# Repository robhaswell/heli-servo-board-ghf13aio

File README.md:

# Helicopter servo bus board
This project is a PCB designed to facilitate wiring a helicopter servo bus to a drone flight controller.

Mounting pattern: 16x16mm

The flight controller in mind when designing this PCB was a [GHF13AIO](https://www.aliexpress.com/af/ghf13aio.html).
This bus supports 3 servo outputs and so must be used for helicopters with a motor-driven tail connected to an ESC.

The connector footprints are for 1.25mm pitch connectors, such as Molex PicoBlade or JST 1.25.

**Please read the [assembly instructions](#assembly-instructions) before ordering or use**

## Instructions for ordering

First: Read the [assembly instructions](#assembly-instructions) and determine that this board is suitable for your setup.

You can order this PCB with a prototyping service.
Below are instructions for using [JLCPCB](https://jlcpcb.com):

1. Visit https://jlcpcb.com/.
2. Click "Order now' from the menu - do not use the quoting box.
3. Upload the file [gerber.zip](gerber.zip).
4. You may use the default options, but I suggest selecting a thickness of 0.8mm or 1.0mm. I also prefer the black PCBs.
5. Add to basket and check out. Take care to review the shipping options. FedEx is good if you would like this sooner, but there is usually a very cheap option depending on your location.

## Assembly instructions

To assemble you will need:

1. PicoBlade or JST 1.25 connectors to match your servo plugs.
2. JST-XH 2-way horizontal connector `S2B-XH-A(LF)(SN)`  
or  
JST-XH vertical or other 2.54mm connector.  
or  
JST-PH or other 2.00mm connector.

**Pay very close attention to plug wiring, pins and polarities!!!**

There are no standard servo plug pinouts.
Test everything with a multimeter before soldering, and again before powering on.

1. Make sure that your intended servos have the control wire as pin 1 or 3.
2. Solder your servo input connector, or use the solder pads directly. These are the control lines from your PWM servo outputs on your FC. If using solder pads you can solder directly to the wire pads, connector pads, or both. Use silicone glue to secure the wire.
3. Solder your servo connectors so that the control wire is the topmost pin, the row labelled "1".
4. Check the position of your servo positive and negative wires. They should line up with "+" and "-". If they do not (e.g. Blade servos) then you will need to re-pin your power connector or wire it in reverse.
5. Check the pins of your power connector and verify correct pins with a multimeter, then solder.
6. Test all connections a final time.

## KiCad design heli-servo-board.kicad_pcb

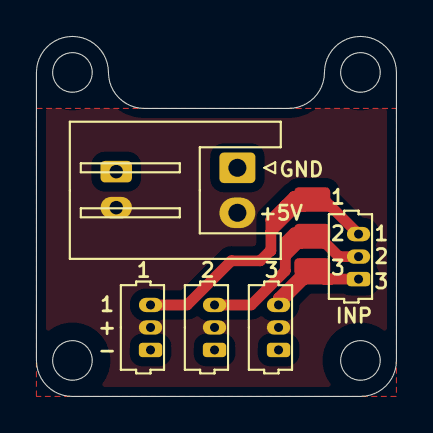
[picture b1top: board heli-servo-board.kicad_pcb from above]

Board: 2 copper layers, 20.0 x 20.0 mm, 12 parts (0 on the bottom side), 5 nets.

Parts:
H1, H2, H3, H4: MountingHole; MountingHole_2.2mm_M2
J1: Conn_01x06; Molex_PicoBlade_53047-0310_1x03_P1.25mm_Vertical
J2, J3, J4: Conn_01x03; Molex_PicoBlade_53047-0310_1x03_P1.25mm_Vertical
J6: Conn_01x02; JST_XH_S2B-XH-A_1x02_P2.50mm_Horizontal
J7, J8, J9: Conn_01x01; SolderWirePad_1x01_SMD_1x2mm

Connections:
+BATT: J2.2, J3.2, J4.2, J6.2
GND: J2.1, J3.1, J4.1, J6.1
unnamed: J1.1, J4.3, J9.1
unnamed: J1.2, J3.3, J8.1
unnamed: J1.3, J2.3, J7.1

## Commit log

2021-08-12 Initialise repo with finished servo board.
2021-08-12 Add images.
2021-08-12 Add 2.0mm power connectors.
2021-08-12 Add a README file.
2021-08-12 Add links into the README.
2021-08-12 The GHF13AIO is actually 16x16mm, redesigned with this mistake corrected
2021-08-12 Slightly adjust XH horizontal position.
2021-08-12 Beter PCB traces.
2021-08-12 Overdo the traces.
2021-08-13 Fix Y dimension.
2021-08-13 Add K110 tail mount.
